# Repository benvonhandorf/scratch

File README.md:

# scratch

This repo exists as a disorganized place for me to drop code which I may or may not care about.  Assume everything here has no value.

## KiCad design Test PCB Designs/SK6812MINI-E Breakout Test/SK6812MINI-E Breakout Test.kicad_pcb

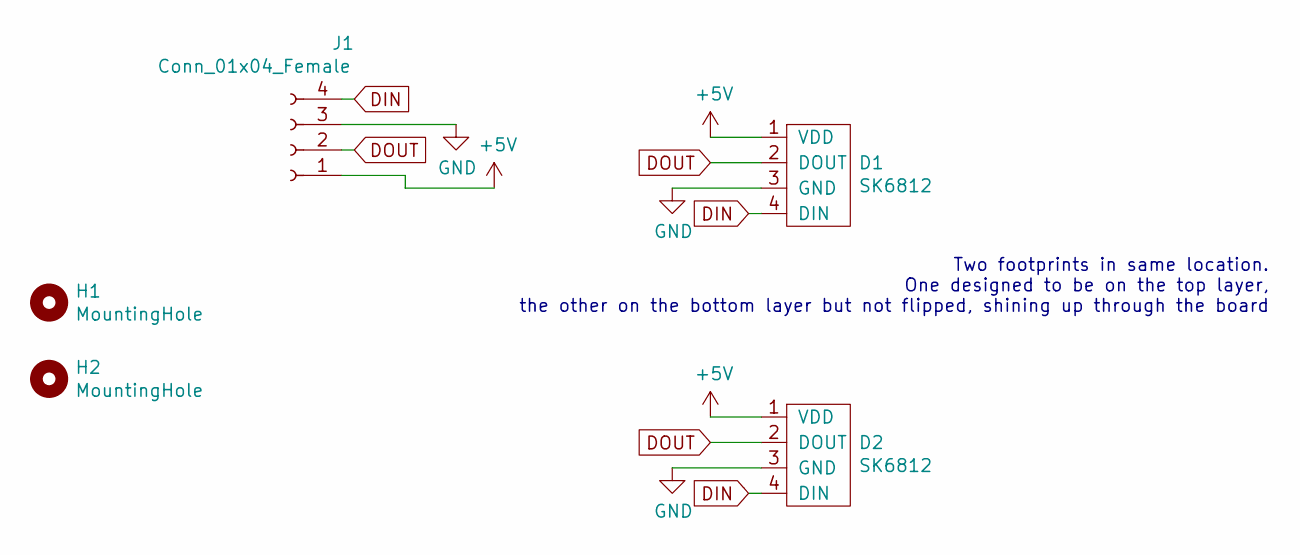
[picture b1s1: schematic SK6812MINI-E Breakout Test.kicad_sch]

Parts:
D1: SK6812; SK6812Mini-E_Front
D2: SK6812; SK6812Mini-E_Back_Shining_Through
H1, H2: MountingHole
J1: Conn_01x04_Female; PinSocket_1x04_P2.54mm_Vertical

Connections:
+5V: D1.1 (VDD), D2.1 (VDD), J1.1
DIN: D1.4 (DIN), D2.4 (DIN), J1.4
DOUT: D1.2 (DOUT), D2.2 (DOUT), J1.2
GND: D1.3 (GND), D2.3 (GND), J1.3

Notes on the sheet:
Two footprints in same location. One designed to be on the top layer, the other on the bottom layer but not flipped, shining up through the board

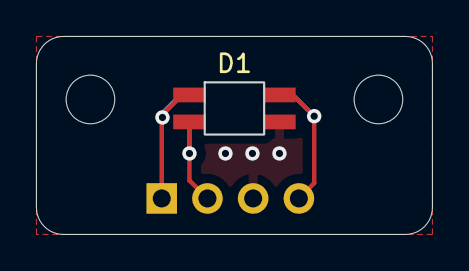
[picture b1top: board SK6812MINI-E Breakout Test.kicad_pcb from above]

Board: 2 copper layers, 21.9 x 10.9 mm, 5 parts (1 on the bottom side), 4 nets.

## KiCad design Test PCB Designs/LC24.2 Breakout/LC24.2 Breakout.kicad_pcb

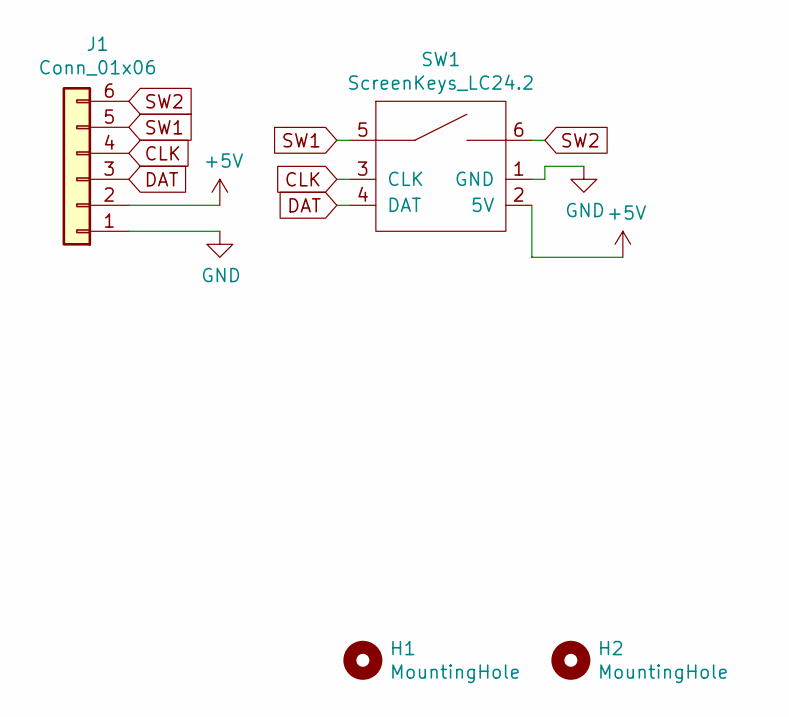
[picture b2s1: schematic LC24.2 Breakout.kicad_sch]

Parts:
H1, H2: MountingHole; MountingHole_3.2mm_M3
J1: Conn_01x06; JST_PH_B6B-PH-K_1x06_P2.00mm_Vertical
SW1: ScreenKeys_LC24.2; ScreenKey_LC24.2

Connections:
+5V: J1.2, SW1.2 (5V)
CLK: J1.4, SW1.3 (CLK)
DAT: J1.3, SW1.4 (DAT)
GND: J1.1, SW1.1 (GND)
SW1: J1.5, SW1.5
SW2: J1.6, SW1.6

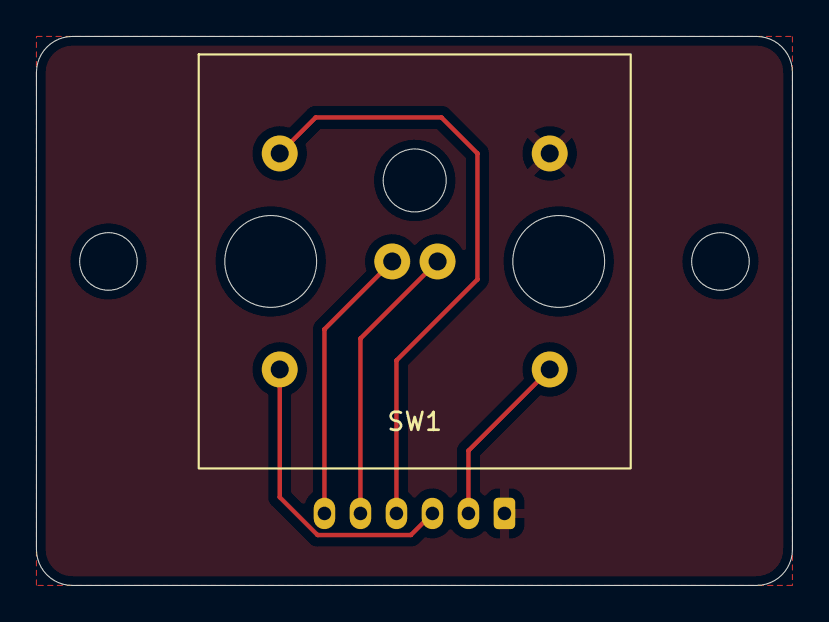
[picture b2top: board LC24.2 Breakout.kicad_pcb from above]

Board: 2 copper layers, 42.0 x 30.5 mm, 4 parts (1 on the bottom side), 6 nets.

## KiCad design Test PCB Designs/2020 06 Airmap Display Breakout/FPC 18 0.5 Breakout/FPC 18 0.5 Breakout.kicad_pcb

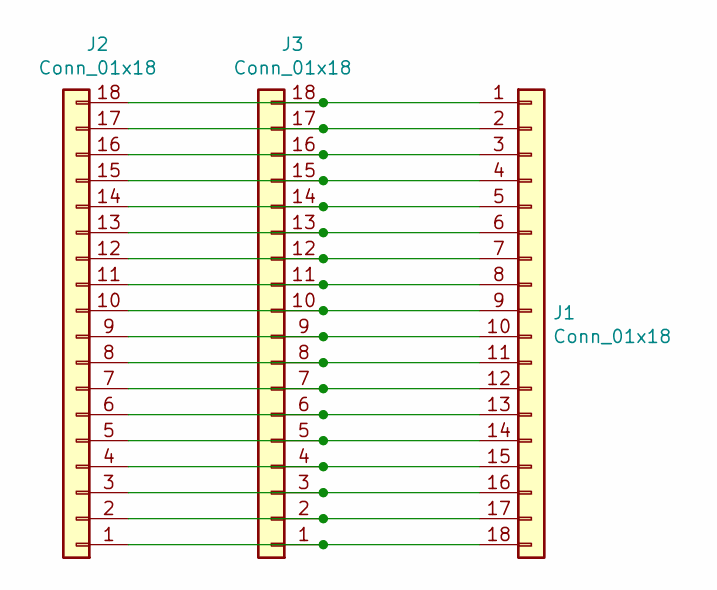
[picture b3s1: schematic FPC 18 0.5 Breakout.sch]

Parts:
J1, J3: Conn_01x18; Molex_WM8831CT-ND
J2: Conn_01x18; PinHeader_1x18_P2.54mm_Vertical

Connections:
unnamed: J1.1, J2.18, J3.18
unnamed: J1.2, J2.17, J3.17
unnamed: J1.3, J2.16, J3.16
unnamed: J1.4, J2.15, J3.15
unnamed: J1.5, J2.14, J3.14
unnamed: J1.6, J2.13, J3.13
unnamed: J1.7, J2.12, J3.12
unnamed: J1.8, J2.11, J3.11
unnamed: J1.9, J2.10, J3.10
unnamed: J1.10, J2.9, J3.9
unnamed: J1.11, J2.8, J3.8
unnamed: J1.12, J2.7, J3.7
unnamed: J1.13, J2.6, J3.6
unnamed: J1.14, J2.5, J3.5
unnamed: J1.15, J2.4, J3.4
unnamed: J1.16, J2.3, J3.3
unnamed: J1.17, J2.2, J3.2
unnamed: J1.18, J2.1, J3.1

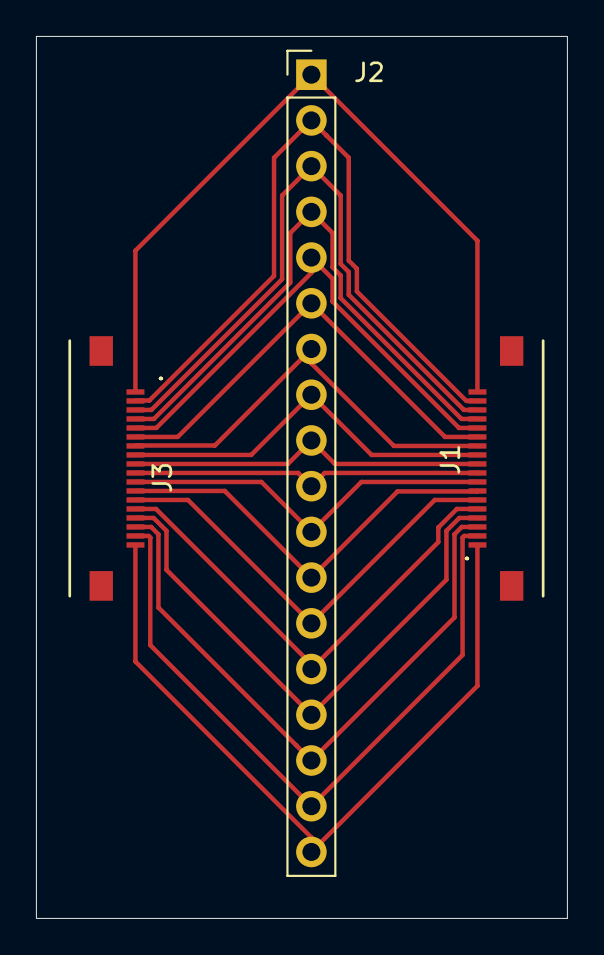
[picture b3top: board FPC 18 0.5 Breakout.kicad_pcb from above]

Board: 2 copper layers, 29.5 x 49.0 mm, 3 parts (0 on the bottom side), 18 nets.

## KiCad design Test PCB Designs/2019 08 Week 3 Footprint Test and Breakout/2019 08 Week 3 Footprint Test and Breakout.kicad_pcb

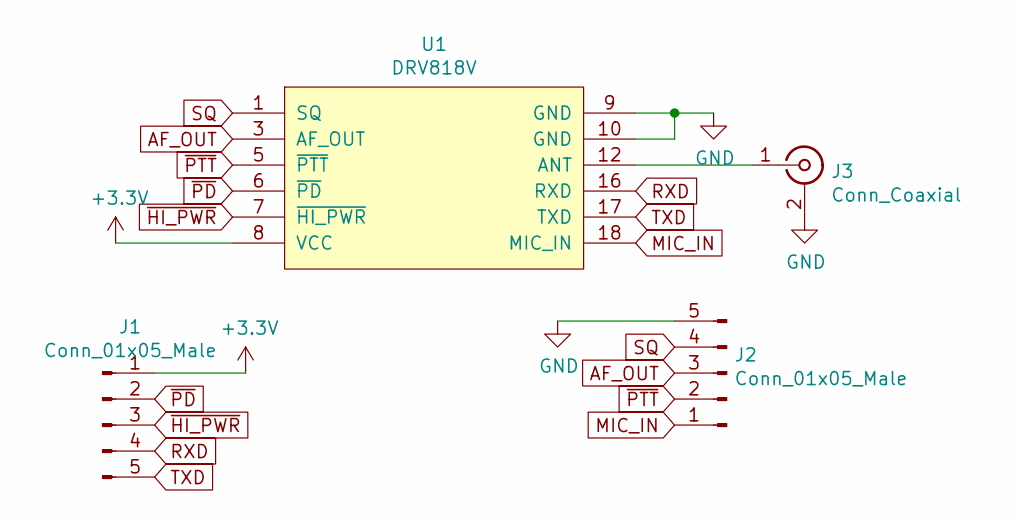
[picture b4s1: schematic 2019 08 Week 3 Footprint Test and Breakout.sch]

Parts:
J1, J2: Conn_01x05_Male; Pin_Header_Straight_1x05_Pitch2.54mm
J3: Conn_Coaxial; SMA_THT_90deg
U1: DRV818V

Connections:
+3V3: J1.1, U1.8 (VCC)
AF_OUT: J2.3, U1.3 (AF_OUT)
GND: J2.5, J3.2 (Ext), U1.9 (GND), U1.10 (GND)
MIC_IN: J2.1, U1.18 (MIC_IN)
unnamed: J3.1 (In), U1.12 (ANT)
RXD: J1.4, U1.16 (RXD)
SQ: J2.4, U1.1 (SQ)
TXD: J1.5, U1.17 (TXD)
~HI_PWR: J1.3, U1.7 (~HI_PWR)
~PD: J1.2, U1.6 (~PD)
~PTT: J2.2, U1.5 (~PTT)

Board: 2 copper layers, 4 parts (0 on the bottom side), 11 nets, no tracks yet.

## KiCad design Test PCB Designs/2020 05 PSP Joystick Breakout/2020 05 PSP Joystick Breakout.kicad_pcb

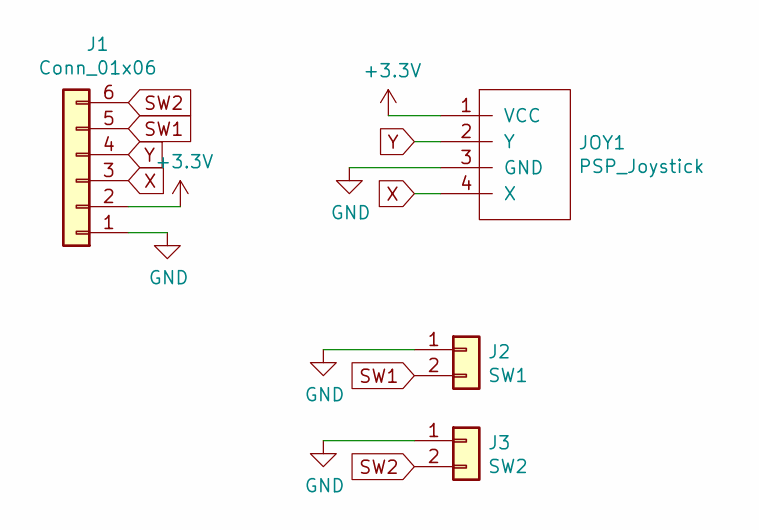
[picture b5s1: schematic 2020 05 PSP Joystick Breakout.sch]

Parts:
J1: Conn_01x06; JST_PH_B6B-PH-K_06x2.00mm_Straight
J2: SW1; Pin_Header_Straight_1x02_Pitch2.54mm
J3: SW2; Pin_Header_Straight_1x02_Pitch2.54mm
JOY1: PSP_Joystick; PSP_Joystick_Hybrid

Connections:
+3V3: J1.2, JOY1.1 (VCC)
GND: J1.1, J2.1, J3.1, JOY1.3 (GND)
SW1: J1.5, J2.2
SW2: J1.6, J3.2
X: J1.3, JOY1.4 (X)
Y: J1.4, JOY1.2 (Y)

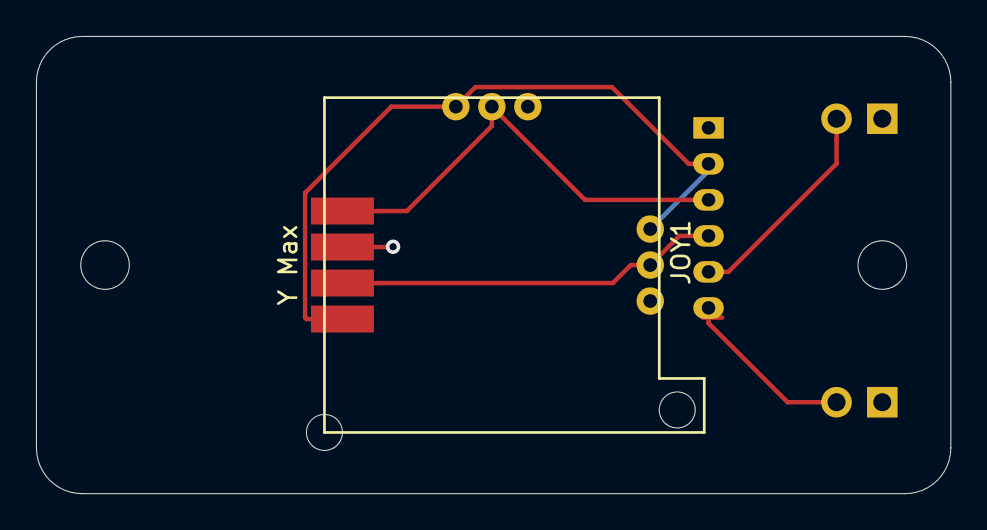
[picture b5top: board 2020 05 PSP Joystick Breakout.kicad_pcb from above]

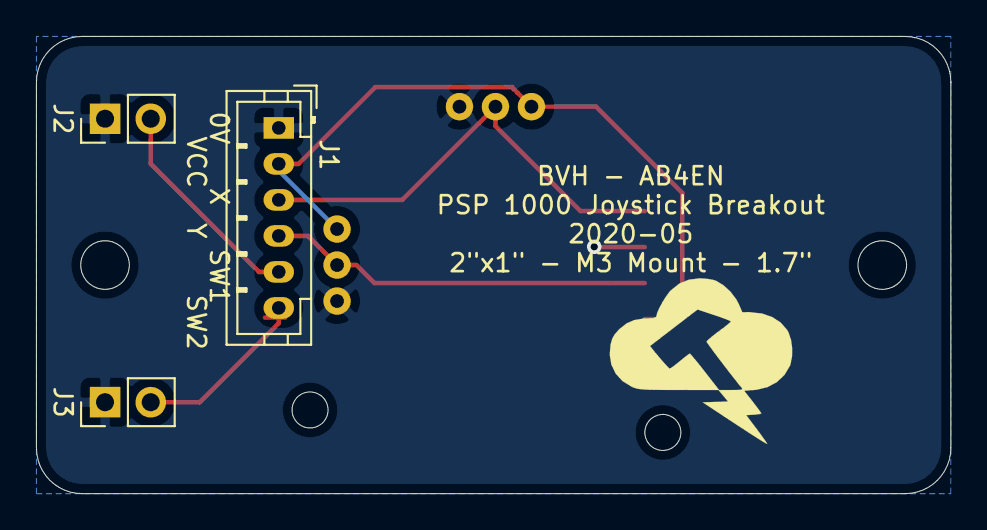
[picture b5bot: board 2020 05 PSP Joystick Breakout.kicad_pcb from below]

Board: 2 copper layers, 50.8 x 25.4 mm, 4 parts (3 on the bottom side), 6 nets.

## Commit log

2018-03-05 Moved esp32 hello_world project into scratch
2018-03-23 Organization
2018-03-23 Another test board
2019-05-04 catchup
2019-05-07 2019 May PCB 1
2019-05-19 WSPR Query and processing
2019-06-26 Initial work on sota qsl card
2019-06-26 static map work
2019-07-06 CW work
2019-07-06 CW Synthesis starting to work
2019-07-07 Timing issues worked out
2019-07-07 fix gitignore
2019-07-07 Usable
2019-07-08 Add polly caching and koch file generation
2019-07-08 Improvements
2019-07-10 Refactor and ability to suppress TTS
2019-07-10 Sota API start
2019-07-11 Reference card construction basics
2019-07-16 Fixes
2019-07-28 Fix bug
2019-08-15 GPX file construction
2019-08-24 Added support for CWOps lessons
2019-08-27 Work on improving sota reference card
2019-08-29 Added speed support
2019-09-27 Scripted
2019-10-20 ADIF CQRLog to POTA log converter - First attempt
2020-01-17 Added hexboard sketch
2020-05-16 PSP Joystick Breakout work
2020-05-17 PSP joystick prototype order
2020-05-29 FPC Breakout Work
2020-06-20 FPC Breakout
2020-06-21 Initial work on ESP8266 BMP board
2020-06-21 ESP8266 BMP design v1
2020-06-23 PAW3204 Breakout WIP
2020-06-24 Moved PAW3204 board to SCR
2020-07-21 Cleanup
2020-08-11 Add gpx
2020-12-30 WIP Macro Keyboard
2020-12-31 Macro keyboard WIP
2021-03-07 Breakout Test Boards 2021-03
